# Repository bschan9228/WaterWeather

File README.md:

# WaterWeather
Projects involving aquariums

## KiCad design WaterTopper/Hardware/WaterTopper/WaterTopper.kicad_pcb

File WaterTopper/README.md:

# WaterTopper
WaterTopper is a device that can automatically pump liquids. Using non-contact liquid level sensors, it can pump water accordingly.

It features:
- ESP32-S3-MINI-1 microcontroller
- USB-C for programming and powering the device
- Barrel jack to power two motors through terminals
- Dual motor drivers to control peristaltic pumps
- Four JST connectors to connect non-contact liquid level sensors
- 240x320 TFT display
- External temperature sensor
- One user-programmable button
- Six user-programmable LEDs

## Schematics

## PCB Design

## Current Hardware Bugs
- Display's MOSFET has the wrong pinout/footprint
- Display's connectors has the wrong size/footprint
- JST connectors have the wrong footprint

- Significant problems with motor driver not working
- Voltage divider dividing incorrectly

Thanks for UCSD Envision/Colin for making this project happen.

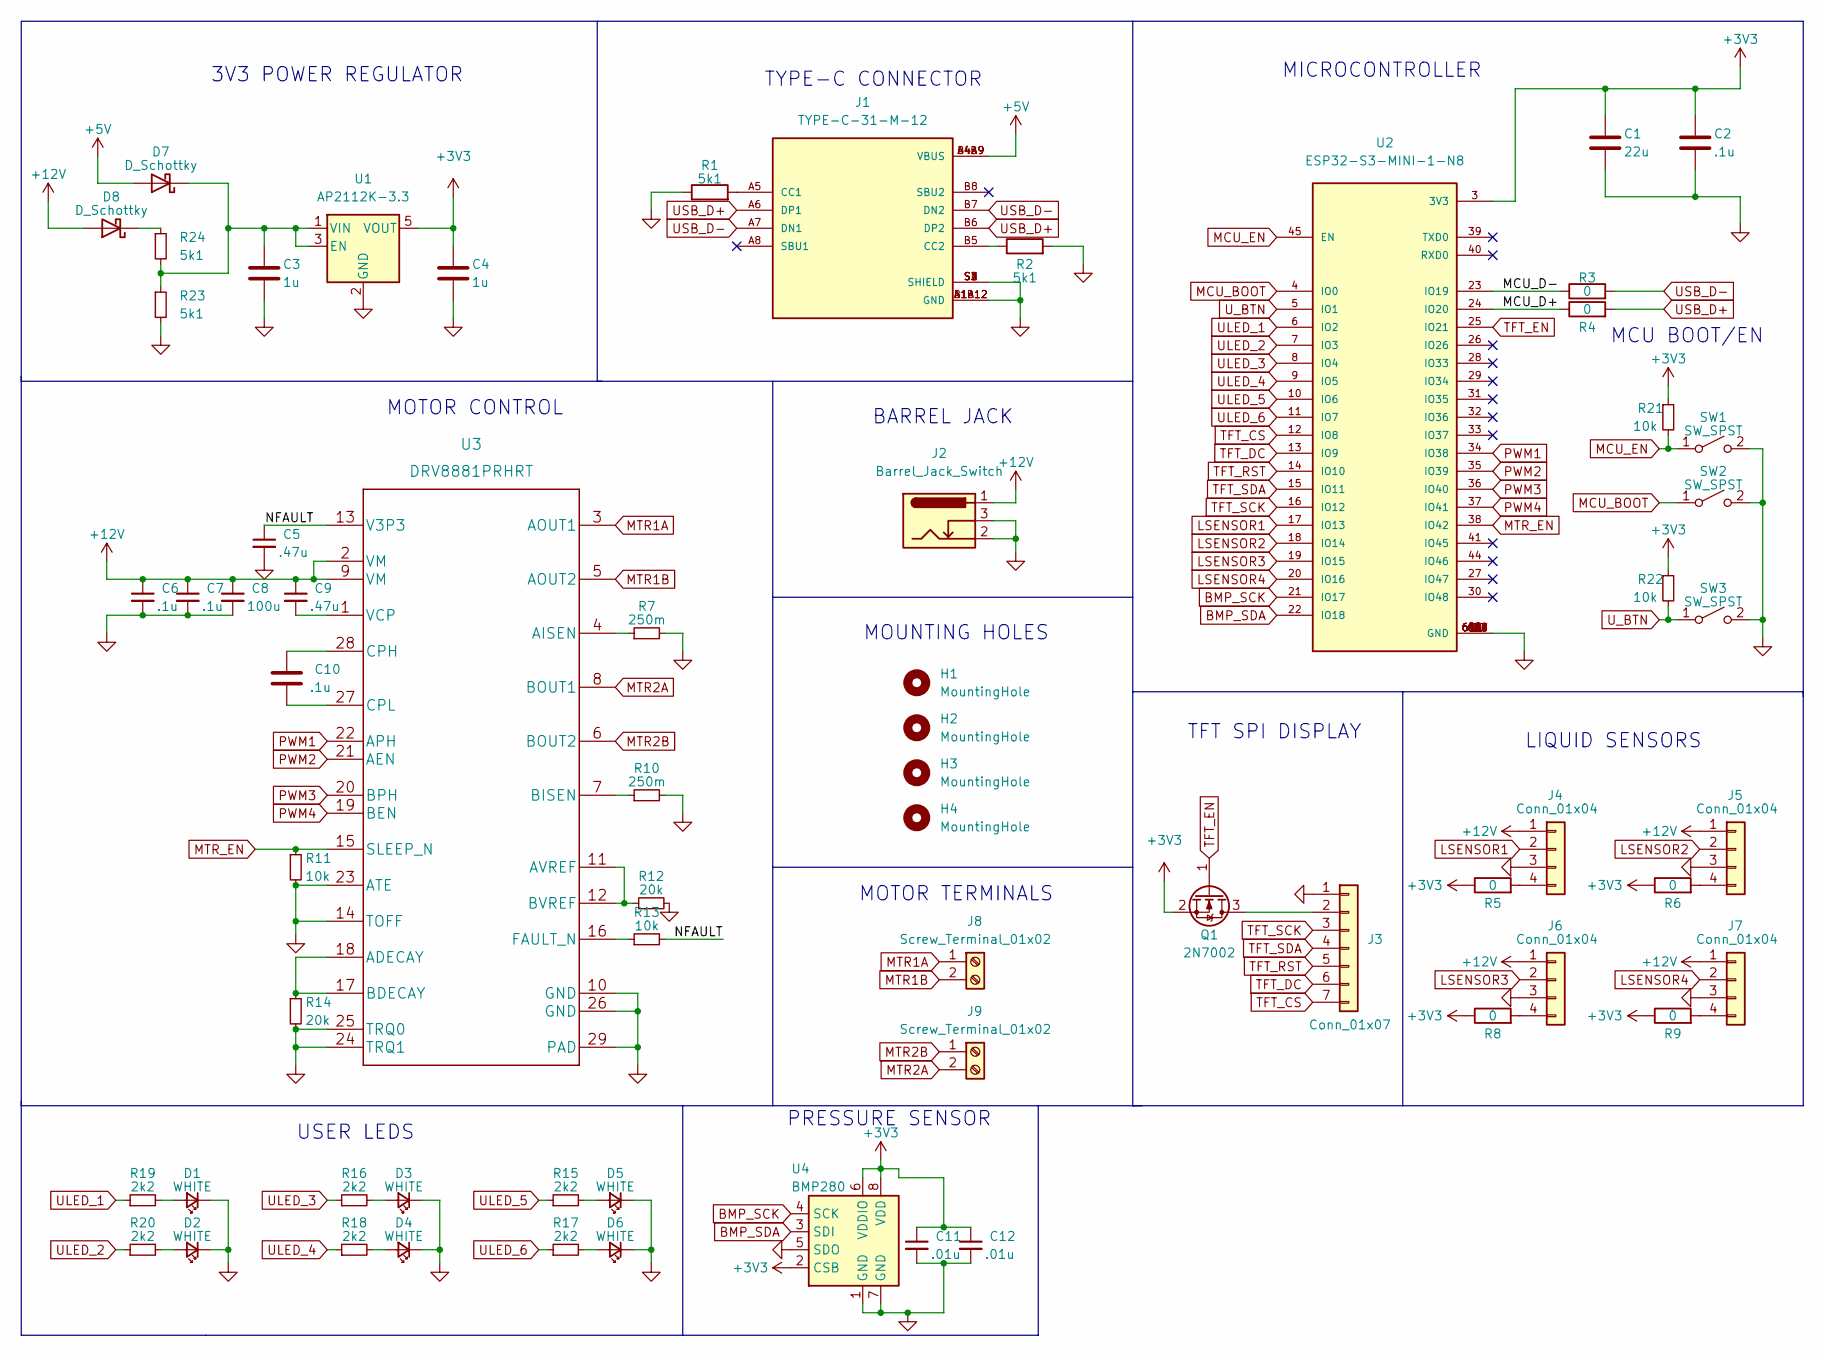
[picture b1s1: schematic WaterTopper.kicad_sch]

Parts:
C1: 22u; C_0805_2012Metric
C2, C6, C7, C10: .1u; C_0603_1608Metric
C3, C4: 1u; C_0805_2012Metric
C5, C9: .47u; C_0603_1608Metric
C8: 100u; C_Elec_6.3x5.8
C11, C12: .01u; C_0603_1608Metric
D1, D2, D3, D4, D5, D6: WHITE; LED_0603_1608Metric
D7, D8: D_Schottky; D_SMA
H1, H2, H3, H4: MountingHole; MountingHole_3.2mm_M3
J1: TYPE-C-31-M-12; HRO_TYPE-C-31-M-12; PARTREV A
J2: Barrel_Jack_Switch; BarrelJack_Wuerth_6941xx301002
J3: Conn_01x07; PinHeader_1x07_P2.00mm_Vertical
J4, J5, J6, J7: Conn_01x04; JST_PH_B4B-PH-K_1x04_P2.00mm_Vertical
J8, J9: Screw_Terminal_01x02; TerminalBlock_bornier-2_P5.08mm
Q1: 2N7002; SOT-23
R1, R2, R23, R24: 5k1; R_0603_1608Metric
R3, R4, R5, R6, R8, R9: 0; R_0603_1608Metric
R7, R10: 250m; R_0603_1608Metric
R11, R13, R21, R22: 10k; R_0603_1608Metric
R12, R14: 20k; R_0603_1608Metric
R15, R16, R17, R18, R19, R20: 2k2; R_0603_1608Metric
SW1, SW2: SW_SPST; SW_SPST_PTS810
SW3: SW_SPST; SW_Tactile_SPST_Angled_PTS645Vx58-2LFS
U1: AP2112K-3.3; SOT-23-5
U2: ESP32-S3-MINI-1-N8; XCVR_ESP32-S3-MINI-1-N8; PARTREV v0.6
U3: DRV8881PRHRT
U4: BMP280; Bosch_LGA-8_2x2.5mm_P0.65mm_ClockwisePinNumbering

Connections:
+3V3: C1.1, C2.1, C4.1, C11.1, C12.1, Q1.2 (S), R5.1, R6.1, R8.1, R9.1, R21.1, R22.1, U1.5 (VOUT), U2.3 (3V3), U4.2 (CSB), U4.6 (VDDIO), U4.8 (VDD)
+5V: D7.2 (A), J1.A4B9 (VBUS), J1.B4A9 (VBUS)
+12V: C6.1, C7.1, C8.1, C9.1, D8.2 (A), J2.1, J4.1, J5.1, J6.1, J7.1, U3.2 (VM), U3.9 (VM)
/MCU_D+: R4.1, U2.24 (IO20)
/MCU_D-: R3.1, U2.23 (IO19)
/NFAULT: C5.1, R13.2, U3.13 (V3P3)
BMP_SCK: U2.21 (IO17), U4.4 (SCK)
BMP_SDA: U2.22 (IO18), U4.3 (SDI)
GND: C1.2, C2.2, C3.2, C4.2, C5.2, C6.2, C7.2, C8.2, C11.2, C12.2, D1.1 (K), D2.1 (K), D3.1 (K), D4.1 (K), D5.1 (K), D6.1 (K), J1.A1B12 (GND), J1.B1A12 (GND), J1.S1 (SHIELD), J1.S2 (SHIELD), J1.S3 (SHIELD), J1.S4 (SHIELD), J2.2, J2.3, J3.1, J4.3, J5.3, J6.3, J7.3, R1.1, R2.2, R7.2, R10.2, R11.2, R12.2, R14.2, R23.2, SW1.2 (B), SW2.2 (B), SW3.2 (B), U1.2 (GND), U2.1 (GND), U2.2 (GND), U2.42 (GND), U2.43 (GND), U2.46 (GND), U2.47 (GND), U2.48 (GND), U2.49 (GND), U2.50 (GND), U2.51 (GND), U2.52 (GND), U2.53 (GND), U2.54 (GND), U2.55 (GND), U2.56 (GND), U2.57 (GND), U2.58 (GND), U2.59 (GND), U2.60 (GND), U2.61 (GND), U2.61_1 (GND), U2.61_2 (GND), U2.61_3 (GND), U2.61_4 (GND), U2.61_5 (GND), U2.61_6 (GND), U2.61_7 (GND), U2.61_8 (GND), U2.62 (GND), U2.63 (GND), U2.64 (GND), U2.65 (GND), U3.10 (GND), U3.14 (TOFF), U3.23 (ATE), U3.24 (TRQ1), U3.25 (TRQ0), U3.26 (GND), U3.29 (PAD), U3.V1, U3.V2, U3.V3, U3.V4, U4.1 (GND), U4.5 (SDO), U4.7 (GND)
LSENSOR1: J4.2, U2.17 (IO13)
LSENSOR2: J5.2, U2.18 (IO14)
LSENSOR3: J6.2, U2.19 (IO15)
LSENSOR4: J7.2, U2.20 (IO16)
MCU_BOOT: SW2.1 (A), U2.4 (IO0)
MCU_EN: R21.2, SW1.1 (A), U2.45 (EN)
MTR1A: J8.1, U3.3 (AOUT1)
MTR1B: J8.2, U3.5 (AOUT2)
MTR2A: J9.2, U3.8 (BOUT1)
MTR2B: J9.1, U3.6 (BOUT2)
MTR_EN: R11.1, U2.38 (IO42), U3.15 (SLEEP_N)
unnamed: C3.1, D7.1 (K), R23.1, R24.2, U1.1 (VIN), U1.3 (EN)
unnamed: C9.2, U3.1 (VCP)
unnamed: C10.1, U3.28 (CPH)
unnamed: C10.2, U3.27 (CPL)
unnamed: D1.2 (A), R19.2
unnamed: D2.2 (A), R20.2
unnamed: D3.2 (A), R16.2
unnamed: D4.2 (A), R18.2
unnamed: D5.2 (A), R15.2
unnamed: D6.2 (A), R17.2
unnamed: D8.1 (K), R24.1
unnamed: J1.A5 (CC1), R1.2
unnamed: J1.B5 (CC2), R2.1
unnamed: J3.2, Q1.3 (D)
unnamed: J4.4, R5.2
unnamed: J5.4, R6.2
unnamed: J6.4, R8.2
unnamed: J7.4, R9.2
unnamed: R7.1, U3.4 (AISEN)
unnamed: R10.1, U3.7 (BISEN)
unnamed: R12.1, U3.11 (AVREF), U3.12 (BVREF)
unnamed: R13.1, U3.16 (FAULT_N)
unnamed: R14.1, U3.17 (BDECAY), U3.18 (ADECAY)
PWM1: U2.34 (IO38), U3.22 (APH)
PWM2: U2.35 (IO39), U3.21 (AEN)
PWM3: U2.36 (IO40), U3.20 (BPH)
PWM4: U2.37 (IO41), U3.19 (BEN)
TFT_CS: J3.7, U2.12 (IO8)
TFT_DC: J3.6, U2.13 (IO9)
TFT_EN: Q1.1 (G), U2.25 (IO21)
TFT_RST: J3.5, U2.14 (IO10)
TFT_SCK: J3.3, U2.16 (IO12)
TFT_SDA: J3.4, U2.15 (IO11)
ULED_1: R19.1, U2.6 (IO2)
ULED_2: R20.1, U2.7 (IO3)
ULED_3: R16.1, U2.8 (IO4)
ULED_4: R18.1, U2.9 (IO5)
ULED_5: R15.1, U2.10 (IO6)
ULED_6: R17.1, U2.11 (IO7)
USB_D+: J1.A6 (DP1), J1.B6 (DP2), R4.2
USB_D-: J1.A7 (DN1), J1.B7 (DN2), R3.2
U_BTN: R22.2, SW3.1 (A), U2.5 (IO1)

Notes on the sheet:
3V3 POWER REGULATOR
LIQUID SENSORS
MCU BOOT/EN
USER LEDS
MOUNTING HOLES
MOTOR CONTROL
MOTOR TERMINALS
TFT SPI DISPLAY
BARREL JACK
PRESSURE SENSOR
TYPE-C CONNECTOR
MICROCONTROLLER

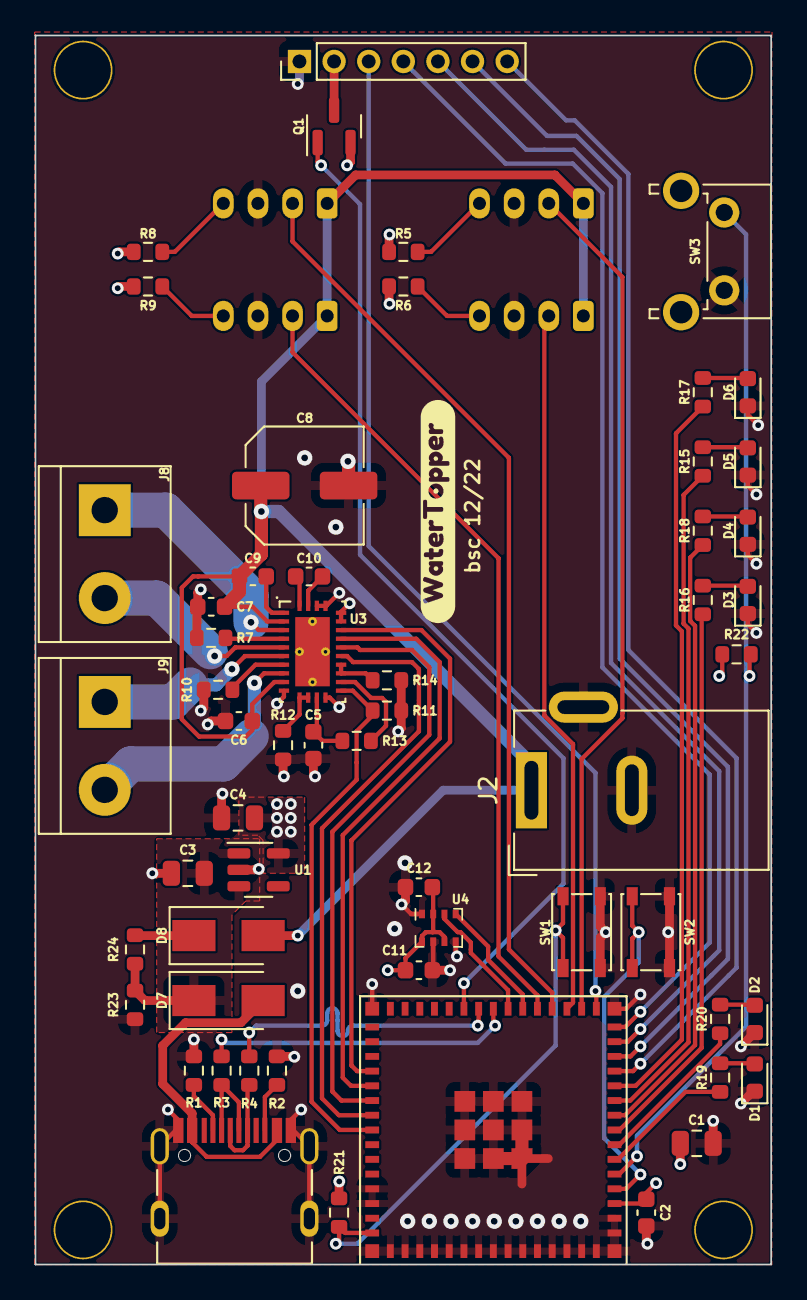
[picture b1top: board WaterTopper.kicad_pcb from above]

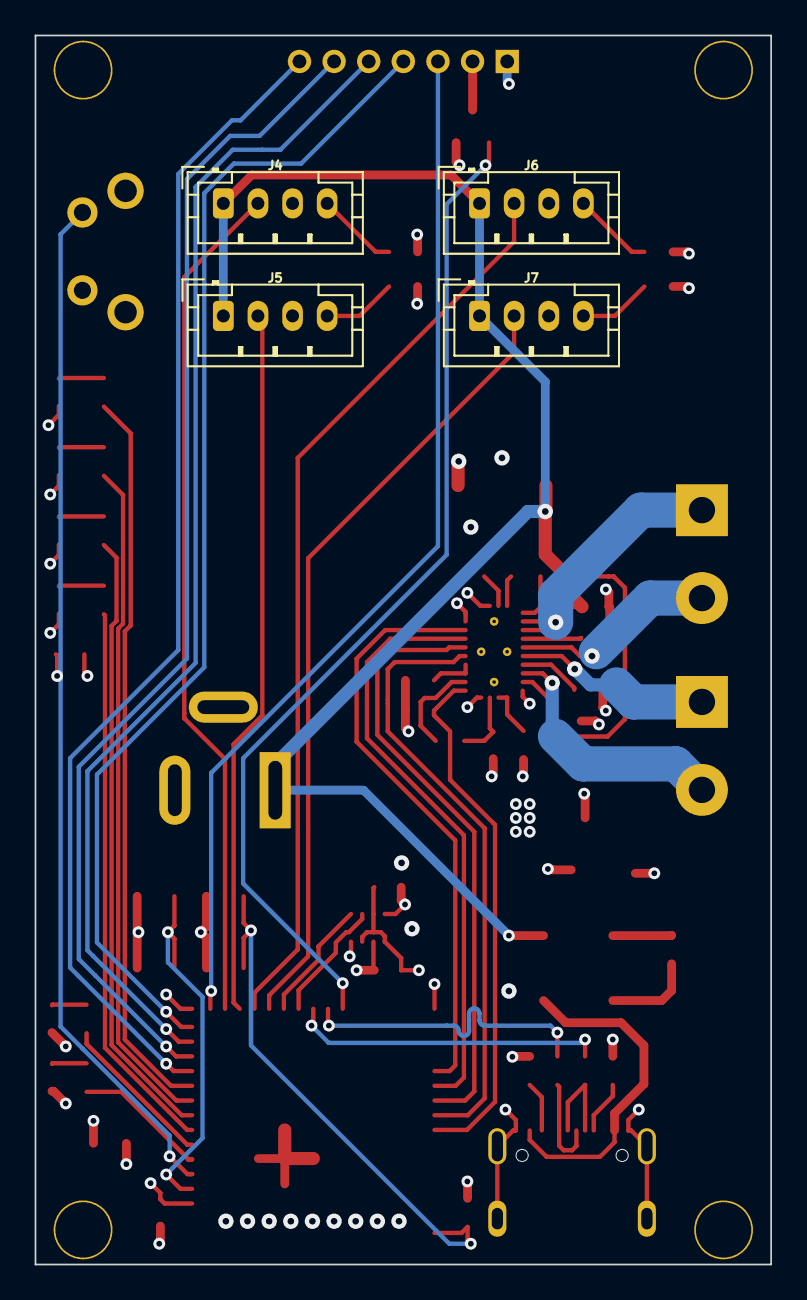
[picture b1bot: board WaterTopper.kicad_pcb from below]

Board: 4 copper layers, 42.5 x 71.0 mm, 66 parts (4 on the bottom side), 62 nets.

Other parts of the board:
kibuzzard-637B1446: G***; kibuzzard-637B1446

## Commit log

2022-11-01 Added testing software files
2022-11-13 Added code for motor control/sensors/display
2022-11-18 Updated and added more parts to schematics
2022-11-20 Finished WaterTopper schematic
2022-11-20 Updated pcb design
2022-11-21 Updated pcb + 4 layer
2022-11-21 Completed pcb v0.1
2022-11-21 Added/fixed silkscreen
2022-11-21 Added small fixes + transistor for display
2022-11-21 Added button
2022-11-21 Added BOM, added voltage divider
2022-12-05 Added bom
2022-12-12 Built small motor driver library
2022-12-12 Made small motor driver library
2022-12-13 Implemented motor driver interrupts
2022-12-15 Begin idf software
2022-12-15 Added websockets & simple html page
2022-12-15 Implemented scuffed auto updaing temp
2022-12-16 Added rtos blink

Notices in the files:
parts and their libraries:
Copyright 2021 Accelerated Designs. All rights reserved.
